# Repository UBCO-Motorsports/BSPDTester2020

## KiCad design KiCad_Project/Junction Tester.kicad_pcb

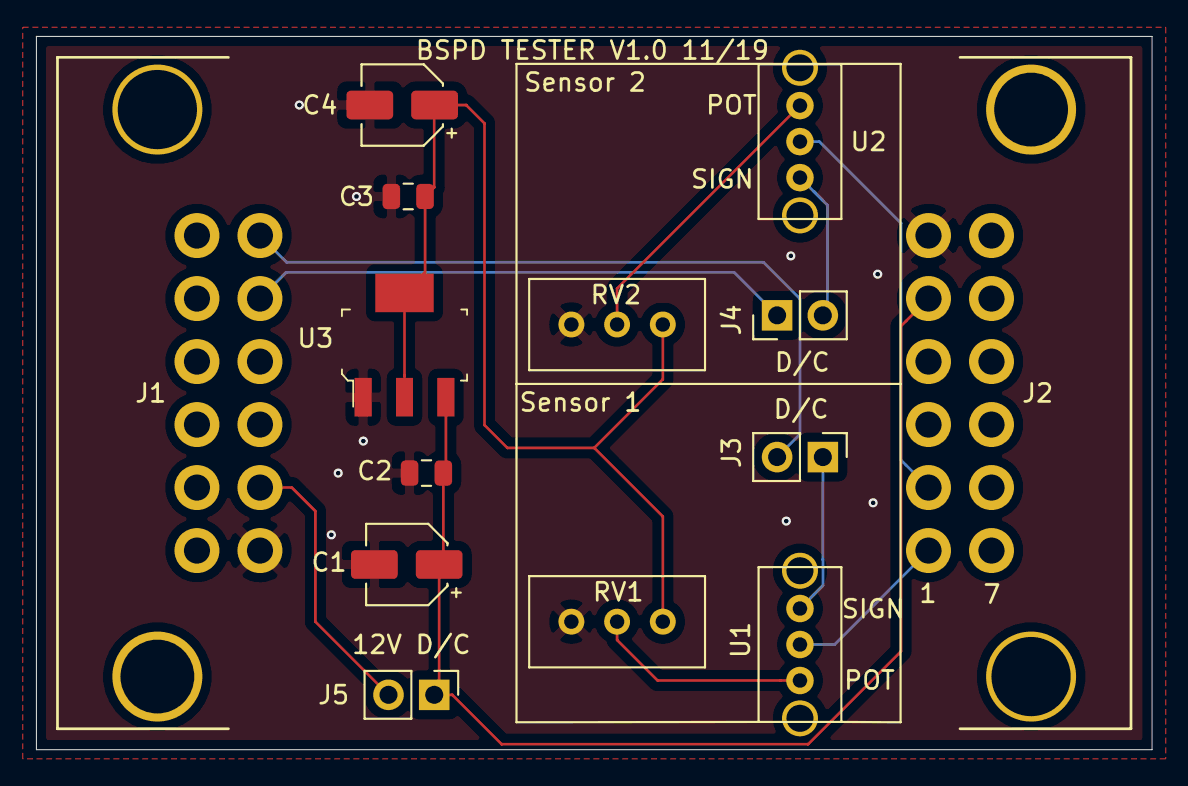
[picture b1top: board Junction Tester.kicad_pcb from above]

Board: 2 copper layers, 62.0 x 39.6 mm, 14 parts (0 on the bottom side), 12 nets.

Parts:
C1, C4: 10u; CP_Elec_4x5.4
C2, C3: 10n; C_0805_2012Metric
J1, J2: Conn_02x06_Counter_Clockwise; MX120G
J3, J4, J5: Conn_01x02_Male; PinHeader_1x02_P2.54mm_Vertical
RV1, RV2: R_POT; Potentiometer_Bourns_3296W_Vertical
U1, U2: 3PoleSwitch; OS102011MS2QN1
U3: NCP1117-1.5_SOT223; SOT-223-4

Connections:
+5V: C3.1, C4.1, RV1.1, RV2.1, U3.2, U3.4
+12V: C1.1, C2.1, J2.5, J5.1, U3.3
GND: C1.2, C2.2, C3.2, C4.2, J1.6, J2.6, RV1.3, RV2.3, U3.1
unnamed: J1.5, J5.2
unnamed: J3.1, U1.3
unnamed: J4.2, U2.1
unnamed: RV1.2, U1.1
unnamed: RV2.2, U2.3
PIN1: J2.1, U1.2
PIN2: J2.2, U2.2
SENS1: J1.1, J3.2
SENS2: J1.2, J4.1

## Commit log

2019-11-21 Added KiCad project to repo
2019-11-22 Clarified some silk screen
